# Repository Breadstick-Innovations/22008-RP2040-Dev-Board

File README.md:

# RP2040 Dev Board
I wanted to get myself more aquainted with JLCPCB's SMT assembly service, so I designed a board to their specs and tried to use their basic parts wherever possible, to minimize $3 loading fees for extended parts. My hope is to save time for others who are also interested in the RP2040 and JLCPCB's assembly service. If you put this design in your KiCad templates folder, it'll be quick and easy to iterate from.

 [Here's a link to the dev thread on Twitter.](https://twitter.com/RangenMichael/status/1531419000948723712?s=20&t=70S1JhFAgyq_hug58spnyA)
 
## Where To Buy
* [Tindie](https://www.tindie.com/products/breadstick/rp2040-dev-board/)
* [Breadstick.ca](https://shop.breadstick.ca/products/rp2040-dev-board)

## CircuitPython (Adafruit)
* [Firmware (.uf2)](https://circuitpython.org/board/raspberry_pi_pico/)
* [Tutorial](https://learn.adafruit.com/getting-started-with-raspberry-pi-pico-circuitpython/overview)
* [Essentials](https://learn.adafruit.com/circuitpython-essentials)
* [Docs](https://docs.circuitpython.org/en/latest/docs/index.html)
* [Mu (CircuitPython Code Editor)](https://codewith.mu/)
* 

## MicroPython
* [Firmware (.uf2)](https://micropython.org/download/rp2-pico/)
* [Tutorial](https://www.youtube.com/watch?v=JCk9QaCH5QU&list=PLEBQazB0HUyQO6rJxKr2umPCgmfAU-cqR&index=6)
* [QuickRef](https://docs.micropython.org/en/latest/rp2/quickref.html)
* [Docs](https://docs.micropython.org/en/latest/index.html)
* [Thonny (Python IDE)](https://thonny.org/)

## Mechanical Drawing

## Fritzing Model (Work In Progress)

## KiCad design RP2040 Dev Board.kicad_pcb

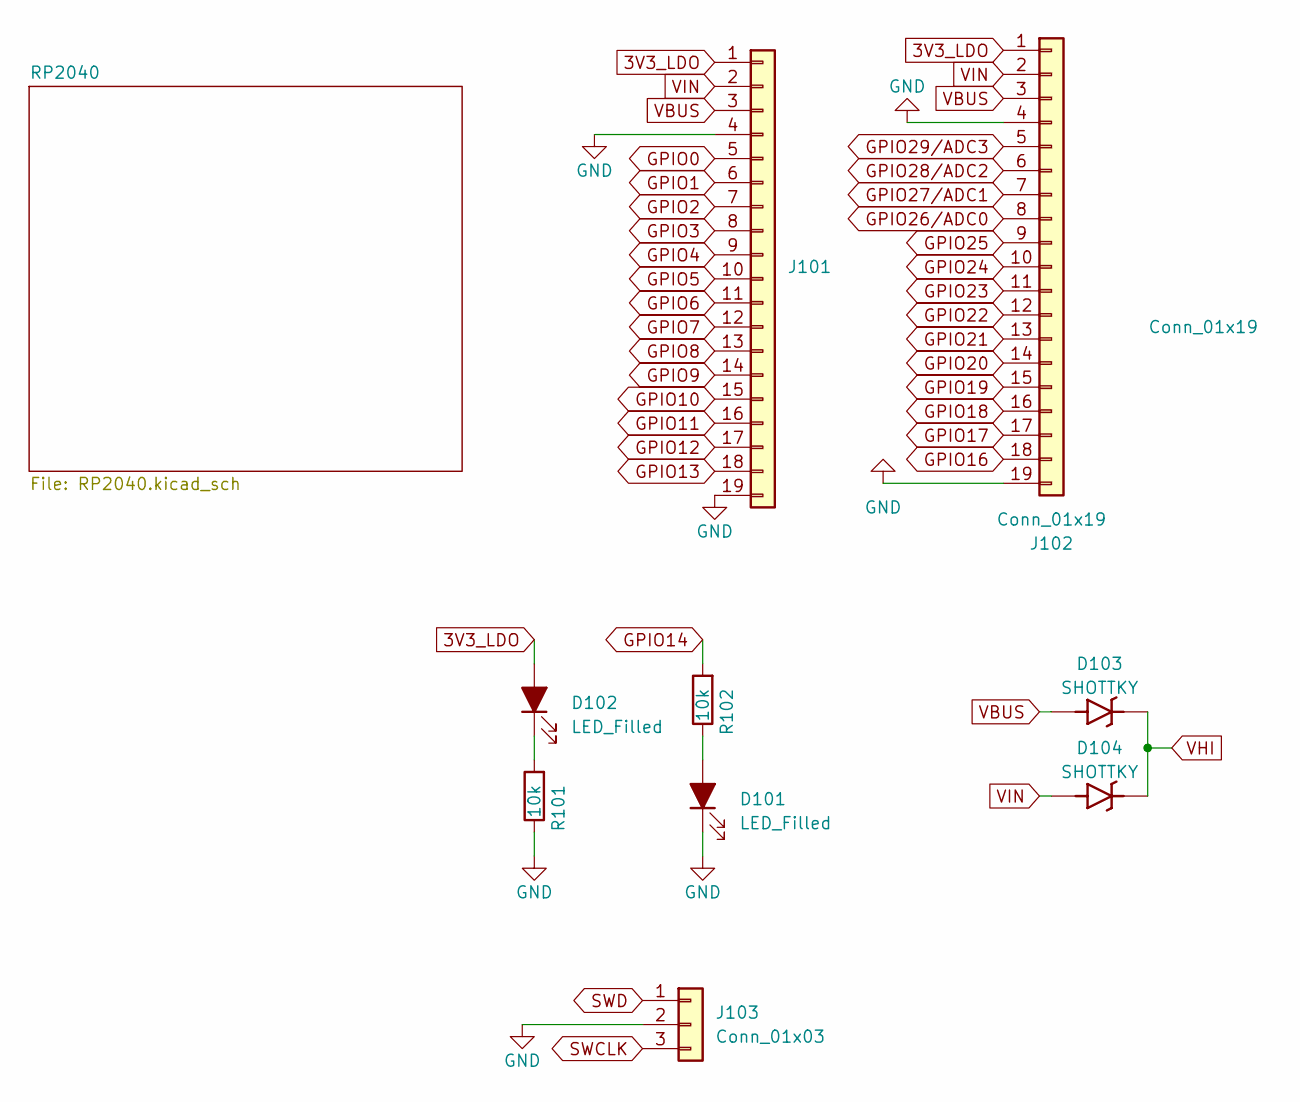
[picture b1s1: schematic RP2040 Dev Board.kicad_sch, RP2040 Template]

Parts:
D101, D102: LED_Filled; LED_0805_2012Metric; JLCPCB P/N C2297
D103, D104: SHOTTKY; D_SOD-123; JLCPCB P/N C8598
J101, J102: Conn_01x19; PinHeader_1x19_P2.54mm_Vertical
J103: Conn_01x03; PinHeader_1x03_P2.54mm_Horizontal
R101, R102: 10k; Perfect_0402_Resistor; JLCPCB P/N C25744

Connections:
3V3_LDO: D102.2 (A), J101.1, J102.1; also elsewhere on the board
GND: D101.1 (K), J101.4, J101.19, J102.4, J102.19, J103.2, R101.1; also elsewhere on the board
GPIO0: J101.5; also elsewhere on the board
GPIO1: J101.6; also elsewhere on the board
GPIO2: J101.7; also elsewhere on the board
GPIO3: J101.8; also elsewhere on the board
GPIO4: J101.9; also elsewhere on the board
GPIO5: J101.10; also elsewhere on the board
GPIO6: J101.11; also elsewhere on the board
GPIO7: J101.12; also elsewhere on the board
GPIO8: J101.13; also elsewhere on the board
GPIO9: J101.14; also elsewhere on the board
GPIO10: J101.15; also elsewhere on the board
GPIO11: J101.16; also elsewhere on the board
GPIO12: J101.17; also elsewhere on the board
GPIO13: J101.18; also elsewhere on the board
GPIO14: R102.2; also elsewhere on the board
GPIO16: J102.18; also elsewhere on the board
GPIO17: J102.17; also elsewhere on the board
GPIO18: J102.16; also elsewhere on the board
GPIO19: J102.15; also elsewhere on the board
GPIO20: J102.14; also elsewhere on the board
GPIO21: J102.13; also elsewhere on the board
GPIO22: J102.12; also elsewhere on the board
GPIO23: J102.11; also elsewhere on the board
GPIO24: J102.10; also elsewhere on the board
GPIO25: J102.9; also elsewhere on the board
GPIO26/ADC0: J102.8; also elsewhere on the board
GPIO27/ADC1: J102.7; also elsewhere on the board
GPIO28/ADC2: J102.6; also elsewhere on the board
GPIO29/ADC3: J102.5; also elsewhere on the board
unnamed: D101.2 (A), R102.1
unnamed: D102.1 (K), R101.2
SWCLK: J103.3; also elsewhere on the board
SWD: J103.1; also elsewhere on the board
VBUS: D103.2 (A), J101.3, J102.3; also elsewhere on the board
VHI: D103.1 (C), D104.1 (C); also elsewhere on the board
VIN: D104.2 (A), J101.2, J102.2

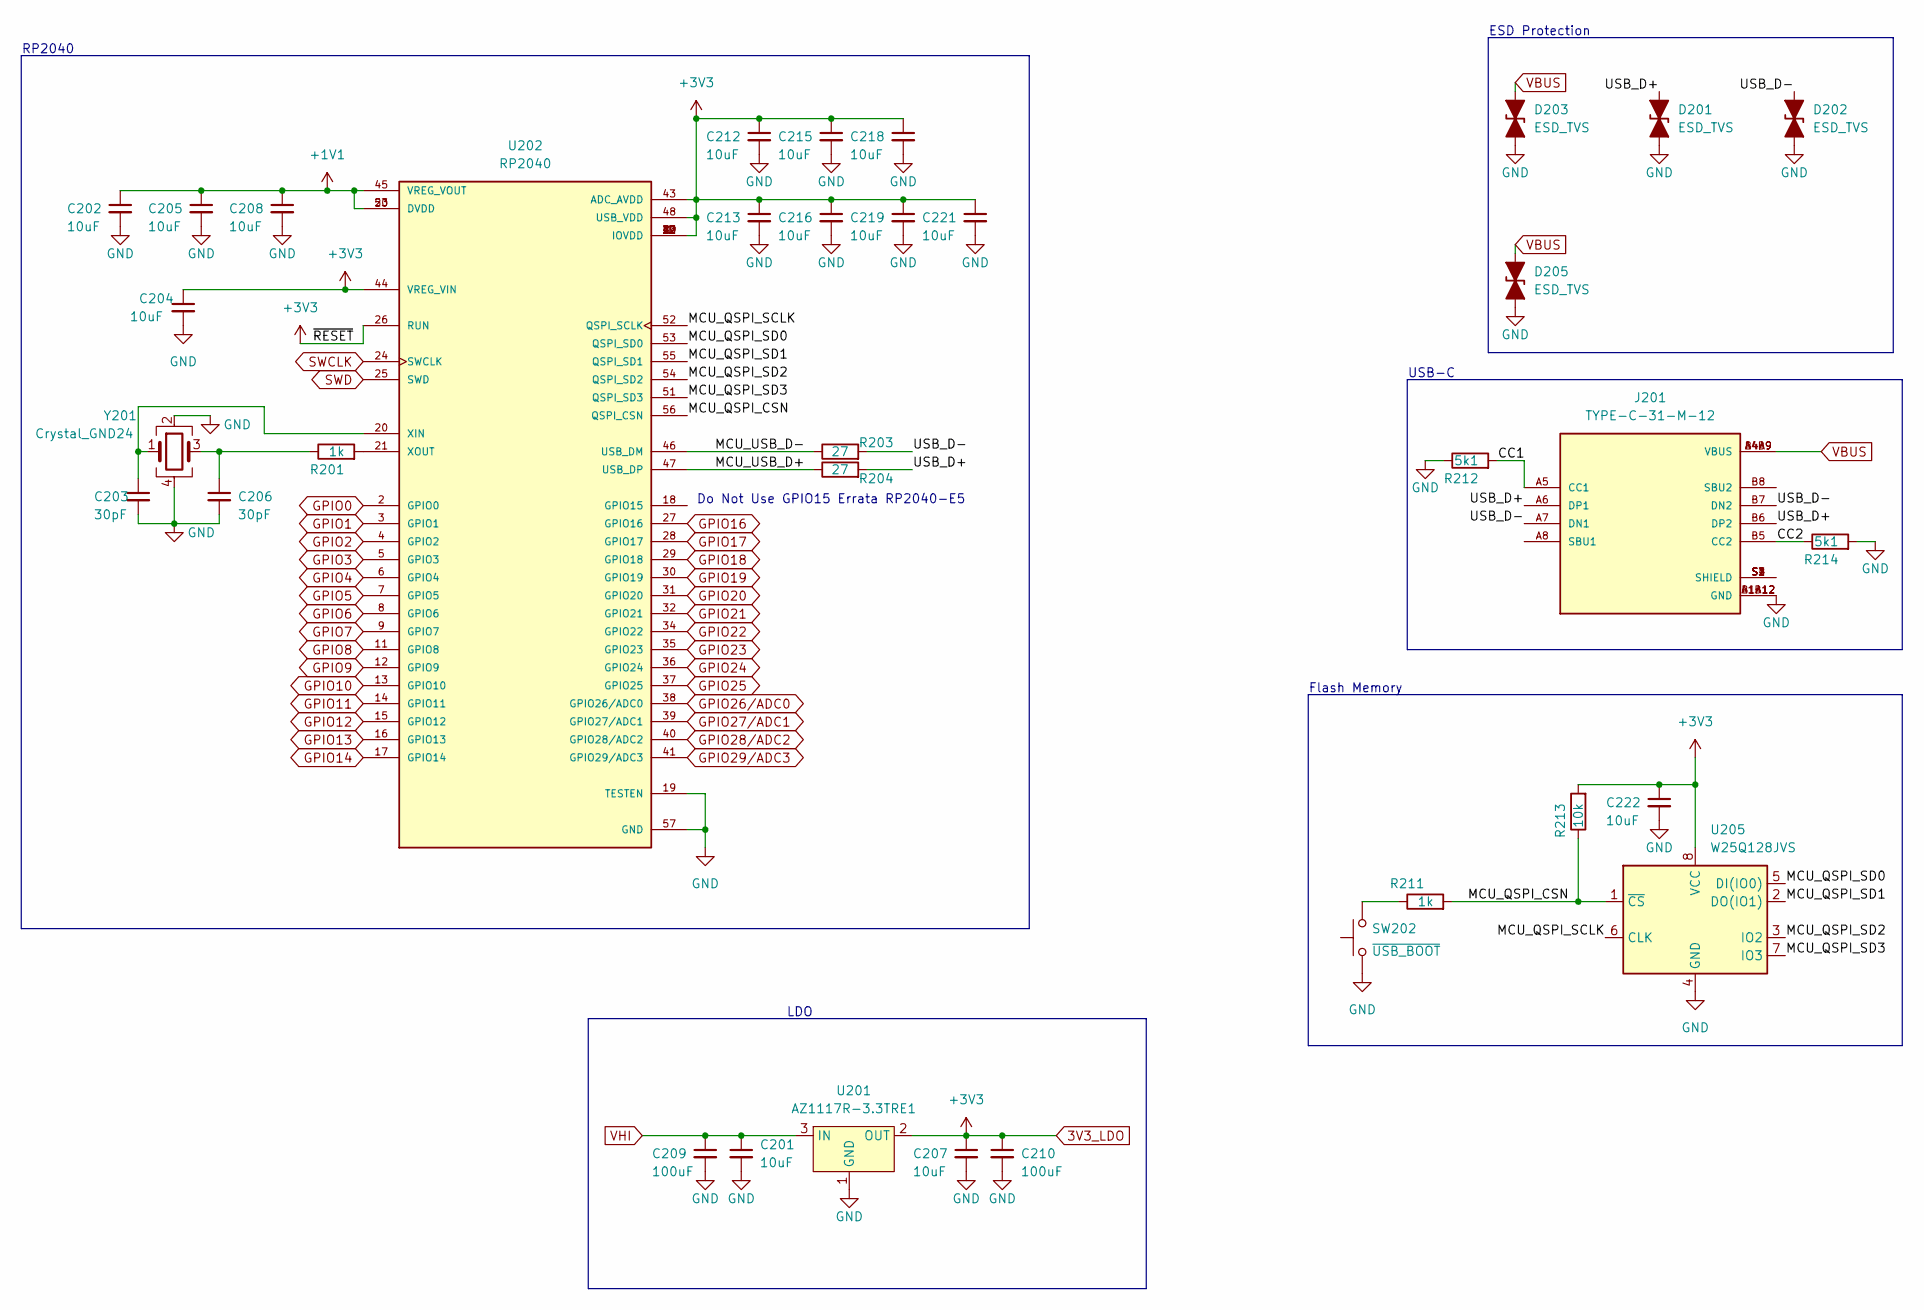
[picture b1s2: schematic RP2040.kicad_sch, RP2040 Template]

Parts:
C201, C202, C204, C205, C207, C208, C212, C213, C215, C216, C218, C219, C221, C222: 10uF; Perfect_0402_Cap; JLCPCB P/N C15525
C203, C206: 30pF; Perfect_0402_Cap; JLCPCB P/N C1570
C209, C210: 100uF; C_1206_3216Metric; JLCPCB P/N C15008
D201, D202, D203, D205: ESD_TVS; Perfect_0402_Resistor; JLCPCB P/N C316049
J201: TYPE-C-31-M-12; HRO_TYPE-C-31-M-12; PARTREV A; JLCPCB P/N C165948
R201, R211: 1k; Perfect_0402_Resistor; JLCPCB P/N C11702
R203, R204: 27; Perfect_0402_Resistor; JLCPCB P/N C25100
R212, R214: 5k1; Perfect_0402_Resistor; JLCPCB P/N C25905
R213: 10k; Perfect_0402_Resistor; JLCPCB P/N C25744
SW202: ~{USB_BOOT}; GT-TC029B-H025-L1N; JLCPCB P/N C843669
U201: AZ1117R-3.3TRE1; SOT-89-3; JLCPCB P/N C108493
U202: RP2040; QFN40P700X700X90-57N; PARTREV 1.6.1; JLCPCB P/N C2040
U205: W25Q128JVS; SOIC-8_5.23x5.23mm_P1.27mm; JLCPCB P/N C97521
Y201: Crystal_GND24; OSC_X322516MLB4SI; JLCPCB P/N C9002

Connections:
3V3_LDO: C204.1, C207.1, C210.1, C212.1, C213.1, C215.1, C216.1, C218.1, C219.1, C221.1, C222.1, R213.2, U201.2 (OUT), U202.1 (IOVDD), U202.10 (IOVDD), U202.22 (IOVDD), U202.26 (RUN), U202.33 (IOVDD), U202.42 (IOVDD), U202.43 (ADC_AVDD), U202.44 (VREG_VIN), U202.48 (USB_VDD), U202.49 (IOVDD), U205.8 (VCC); also elsewhere on the board
+1V1: C202.1, C205.1, C208.1, U202.23 (DVDD), U202.45 (VREG_VOUT), U202.50 (DVDD)
/RP2040/CC1: J201.A5 (CC1), R212.2
/RP2040/CC2: J201.B5 (CC2), R214.1
/RP2040/MCU_QSPI_CSN: R211.2, R213.1, U202.56 (QSPI_CSN), U205.1 (~CS)
/RP2040/MCU_QSPI_SCLK: U202.52 (QSPI_SCLK), U205.6 (CLK)
/RP2040/MCU_QSPI_SD0: U202.53 (QSPI_SD0), U205.5 (DI(IO0))
/RP2040/MCU_QSPI_SD1: U202.55 (QSPI_SD1), U205.2 (DO(IO1))
/RP2040/MCU_QSPI_SD2: U202.54 (QSPI_SD2), U205.3 (IO2)
/RP2040/MCU_QSPI_SD3: U202.51 (QSPI_SD3), U205.7 (IO3)
/RP2040/MCU_USB_D+: R204.1, U202.47 (USB_DP)
/RP2040/MCU_USB_D-: R203.1, U202.46 (USB_DM)
/RP2040/USB_D+: D201.2 (A2), J201.A6 (DP1), J201.B6 (DP2), R204.2
/RP2040/USB_D-: D202.2 (A2), J201.A7 (DN1), J201.B7 (DN2), R203.2
GND: C201.2, C202.2, C203.2, C204.2, C205.2, C206.2, C207.2, C208.2, C209.2, C210.2, C212.2, C213.2, C215.2, C216.2, C218.2, C219.2, C221.2, C222.2, D201.1 (A1), D202.1 (A1), D203.1 (A1), D205.1 (A1), J201.A1B12 (GND), J201.B1A12 (GND), R212.1, R214.2, SW202.1, U201.1 (GND), U202.19 (TESTEN), U202.57 (GND), U205.4 (GND), Y201.2, Y201.4; also elsewhere on the board
GPIO0: U202.2 (GPIO0); also elsewhere on the board
GPIO1: U202.3 (GPIO1); also elsewhere on the board
GPIO2: U202.4 (GPIO2); also elsewhere on the board
GPIO3: U202.5 (GPIO3); also elsewhere on the board
GPIO4: U202.6 (GPIO4); also elsewhere on the board
GPIO5: U202.7 (GPIO5); also elsewhere on the board
GPIO6: U202.8 (GPIO6); also elsewhere on the board
GPIO7: U202.9 (GPIO7); also elsewhere on the board
GPIO8: U202.11 (GPIO8); also elsewhere on the board
GPIO9: U202.12 (GPIO9); also elsewhere on the board
GPIO10: U202.13 (GPIO10); also elsewhere on the board
GPIO11: U202.14 (GPIO11); also elsewhere on the board
GPIO12: U202.15 (GPIO12); also elsewhere on the board
GPIO13: U202.16 (GPIO13); also elsewhere on the board
GPIO14: U202.17 (GPIO14); also elsewhere on the board
GPIO16: U202.27 (GPIO16); also elsewhere on the board
GPIO17: U202.28 (GPIO17); also elsewhere on the board
GPIO18: U202.29 (GPIO18); also elsewhere on the board
GPIO19: U202.30 (GPIO19); also elsewhere on the board
GPIO20: U202.31 (GPIO20); also elsewhere on the board
GPIO21: U202.32 (GPIO21); also elsewhere on the board
GPIO22: U202.34 (GPIO22); also elsewhere on the board
GPIO23: U202.35 (GPIO23); also elsewhere on the board
GPIO24: U202.36 (GPIO24); also elsewhere on the board
GPIO25: U202.37 (GPIO25); also elsewhere on the board
GPIO26/ADC0: U202.38 (GPIO26/ADC0); also elsewhere on the board
GPIO27/ADC1: U202.39 (GPIO27/ADC1); also elsewhere on the board
GPIO28/ADC2: U202.40 (GPIO28/ADC2); also elsewhere on the board
GPIO29/ADC3: U202.41 (GPIO29/ADC3); also elsewhere on the board
unnamed: C203.1, U202.20 (XIN), Y201.1
unnamed: C206.1, R201.1, Y201.3
unnamed: J201.S1 (SHIELD), J201.S2 (SHIELD), J201.S3 (SHIELD), J201.S4 (SHIELD)
unnamed: R201.2, U202.21 (XOUT)
unnamed: R211.1, SW202.2
SWCLK: U202.24 (SWCLK); also elsewhere on the board
SWD: U202.25 (SWD); also elsewhere on the board
VBUS: D203.2 (A2), D205.2 (A2), J201.A4B9 (VBUS), J201.B4A9 (VBUS); also elsewhere on the board
VHI: C201.1, C209.1, U201.3 (IN); also elsewhere on the board

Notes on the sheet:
RP2040
Flash Memory
LDO
ESD Protection
USB-C
Do Not Use GPIO15 Errata RP2040-E5

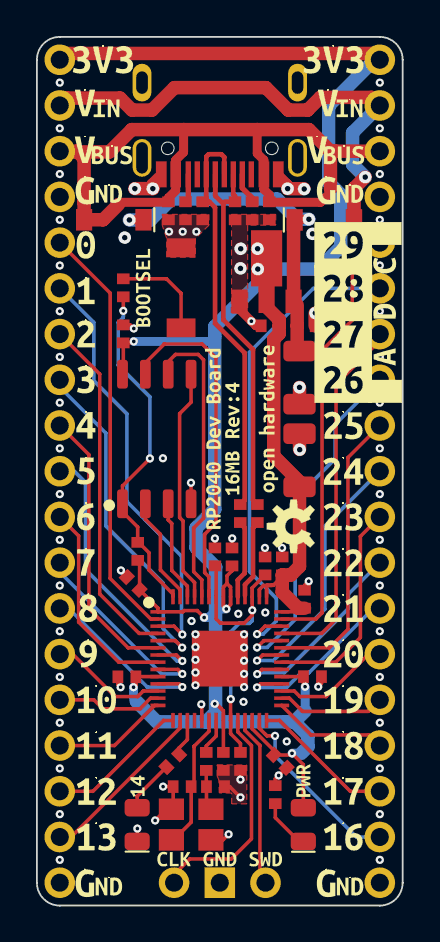
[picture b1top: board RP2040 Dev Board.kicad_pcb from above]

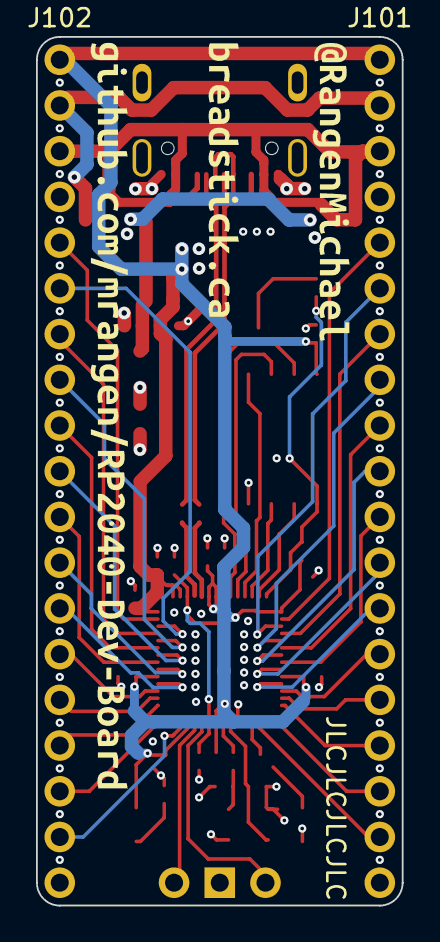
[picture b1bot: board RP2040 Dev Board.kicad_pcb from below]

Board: 4 copper layers, 20.3 x 48.3 mm, 105 parts (5 on the bottom side), 56 nets.

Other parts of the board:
kibuzzard-624A32A0, kibuzzard-624A32A0#2, kibuzzard-624A32A0#3, kibuzzard-624A32A0#4: G***; kibuzzard-624A32A0
kibuzzard-624A32CC, kibuzzard-624A32CC#2: G***; kibuzzard-624A32CC
kibuzzard-624A32F4, kibuzzard-624A32F4#2: G***; kibuzzard-624A32F4
kibuzzard-624A33C6, kibuzzard-624A33C6#2, kibuzzard-624A33C6#3, kibuzzard-624A33C6#4: G***; kibuzzard-624A33C6
kibuzzard-624A33D7, kibuzzard-624A33D7#2, kibuzzard-624A33D7#3, kibuzzard-624A33D7#4: G***; kibuzzard-624A33D7
kibuzzard-624A34DF: G***; kibuzzard-624A34DF
kibuzzard-624A34EB: G***; kibuzzard-624A34EB
kibuzzard-624A34F5: G***; kibuzzard-624A34F5
kibuzzard-624A34FB: G***; kibuzzard-624A34FB
kibuzzard-624A35E6: G***; kibuzzard-624A35E6
kibuzzard-624A35EE: G***; kibuzzard-624A35EE
kibuzzard-624A35F5: G***; kibuzzard-624A35F5
kibuzzard-624A35FE: G***; kibuzzard-624A35FE
kibuzzard-624A352B: G***; kibuzzard-624A352B
kibuzzard-624A353B: G***; kibuzzard-624A353B
kibuzzard-624A355B: G***; kibuzzard-624A355B
kibuzzard-624A358D: G***; kibuzzard-624A358D
kibuzzard-624A359E: G***; kibuzzard-624A359E
kibuzzard-624A3245, kibuzzard-624A3245#2: G***; kibuzzard-624A3245
kibuzzard-624A3524: G***; kibuzzard-624A3524
kibuzzard-624A3534: G***; kibuzzard-624A3534
kibuzzard-624A3542: G***; kibuzzard-624A3542
kibuzzard-624A3549: G***; kibuzzard-624A3549
kibuzzard-624A3554: G***; kibuzzard-624A3554
kibuzzard-624A3563: G***; kibuzzard-624A3563
kibuzzard-624A3578: G***; kibuzzard-624A3578
kibuzzard-624A3580: G***; kibuzzard-624A3580
kibuzzard-624A3587: G***; kibuzzard-624A3587
kibuzzard-624A3594: G***; kibuzzard-624A3594
kibuzzard-6260D8D7: G***; kibuzzard-6260D8D7
kibuzzard-6260D8EE: G***; kibuzzard-6260D8EE
kibuzzard-6260D8FE: G***; kibuzzard-6260D8FE
kibuzzard-6260D95E: G***; kibuzzard-6260D95E
kibuzzard-6260D96B: G***; kibuzzard-6260D96B
kibuzzard-6260D97B: G***; kibuzzard-6260D97B
kibuzzard-6260D939: G***; kibuzzard-6260D939
kibuzzard-6265A538: G***; kibuzzard-6265A538
kibuzzard-62659E4E: G***; kibuzzard-62659E4E
kibuzzard-62659F2B: G***; kibuzzard-62659F2B
kibuzzard-62830DE2: G***; kibuzzard-62830DE2
kibuzzard-628425F6: G***; kibuzzard-628425F6
kibuzzard-6284261D: G***; kibuzzard-6284261D
kibuzzard-6284262A: G***; kibuzzard-6284262A
kibuzzard-6284263D: G***; kibuzzard-6284263D
kibuzzard-6284264D: G***; kibuzzard-6284264D
kibuzzard-62842605: G***; kibuzzard-62842605
kibuzzard-62842613: G***; kibuzzard-62842613
kibuzzard-62842635: G***; kibuzzard-62842635
kibuzzard-62842645: G***; kibuzzard-62842645

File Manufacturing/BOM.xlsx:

Comment | Designator | Footprint | LCSC Part Number
10uF | C201, C202, C204, C205, C207, C208, C212, C213, C215, C216, C218, C219, C221, C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 | 0402 | C15525
30pF | C203, C206 | 0402 | C1570
100uF | C209, C210 | 1206 | C15008
LED_Filled | D101, D102 | 0805 | C2297
SHOTTKY | D103, D104 | SOD-123 | C8598
ESD_TVS | D201, D202, D203, D205 | 0402 | C316049
Conn_01x19 | J101, J102 | Connector_PinHeader_2.54mm:PinHeader_1x19_P2.54mm_Vertical | DNP
Conn_01x03 | J103 | Connector_PinHeader_2.54mm:PinHeader_1x03_P2.54mm_Horizontal | DNP
TYPE-C-31-M-12 | J201 | TYPE-C-31-M-12:HRO_TYPE-C-31-M-12 | C165948
10k | R101, R102, R213 | 0402 | C25744
1k | R201, R211 | 0402 | C11702
27 | R203, R204 | 0402 | C25100
5k1 | R212, R214 | 0402 | C25905
~{USB_BOOT} | SW202 | SW-SMD-2_2.9x3.9x1.7 | C843669
AZ1117R-3.3TRE1 | U201 | SOT-89-3 | C108493
RP2040 | U202 | QFN40P700X700X90-57N | C2040
W25Q128JVS | U205 | SOIC-8_5.23x5.23mm_P1.27mm | C97521
12MHz ±30ppm 20pF 80Ω | Y201 | SMD-3225_4P | C9002

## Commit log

2022-04-23 Initial Commit
    At this point, the design should work. I've routed the 1.1V rail that was missing from the initial prototype and fixed the pads for the LEDs. There's still work to be done, and I haven't ordered this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
2022-04-23 Create README.md
    Added Readme file
2022-04-24 Rev 2
    Ready to order Rev2:
    -Routed missing 1.1V rail
    -Swapped LED footprints from 0603 to 0805
    -Pins 43 &44 routed to nearest decoupling cap
    -Crystal replaced with basic part and created 3D model
    -ADC silkscreen improved
2022-04-24 Generated new pick and place file
    generated new pick and place file and added it to new gerber.zip
2022-04-25 Rev 3
    JLCPCB noticed a mistake in my order, I had remnants from an early version in the gerbers folder. Cleared that out and made some updates to the board and resubmitted as Rev3. I added a GND via that w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
2022-04-27 Typo In BOM
    The LEDs were listed as 0603 in the BOM, updated to 0805.
2022-05-14 backup updated
2022-05-16 Added Photos of Rev3
    Created a photos folder in the main directory and added photos of Rev3
2022-05-17 Made changes to schematic and PCB
    Swapped pin 0 and pin 14.
    Added missing trace from regulator to capacitors.
    Widened power distribution traces.
    Aligned LEDs.
    Adjusted Silkscreen.
    Updated Revision number to 4
2022-05-17 Create FS6xnniUUAUSUpb.png
    Added render of missing trace.
2022-05-17 Backup updated
    This seems to happen whenever the project is opened, even if nothing is changed.
2022-05-17 Increased separation between QSPI bus lines
    Now that the LED is no longer connected to pin 0, there was room to make adjustments that allowed for better separation between the QSPI bus lines.
2022-05-17 Removed unconnected traces found by DRC
    During the last edit, some very short traces that didn't extend beyond the pad they were connected to were overlooked. They've now been deleted and the DRC is coming back clean.
2022-05-17 Modified Silkscreen and Added Renders
    Added OSHW logo and made other silkscreen changes.
    Generated a render of the front of the board.
2022-05-17 Generated New Gerbers, Drill, and Pos files
2022-05-17 Last minute board tweaks
    Made a bunch of small adjustments and made parallel paths for VBUS.
2022-05-18 Final Tweaks New Gerbers
2022-05-18 Backup updated because I reopened the project
2022-05-18 Added Prepreg JLC7628 Note
    The dimensions for the differential USB lines were calculated based off the JLC7628 prepreg.
2022-05-31 None
2022-06-02 Renders and Pinouts Made
2022-06-02 Removed dashes from image names
2022-06-07 Created MicroPython & CircuitPython Pinout Diagrams
2022-06-15 Board Dimensions
    Added board dimensions to User Drawings layer and exported images to the Renders directory. Updated date on both schematic and pcb.
2022-06-15 Generated 3x2 images for Tindie
2022-06-15 Tindie 2x3 Pinouts for CircuitPython & MicroPython
2022-06-22 Create RP2040-Dev-Board.svg
    Began creating SVG model of board for Fritzing

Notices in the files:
RP2040 Dev Board.kicad_pcb:
MIT License
